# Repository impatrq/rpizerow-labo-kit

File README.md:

# rpizerow-labo-kit

Este repositorio cuenta con los esquematicos y circuitos impresos del kit de desarrollo basado en la Raspberry Pi Zero W.

Dentro se encuentran:

- Esquematico y PCB del kit
- Lista de materiales en .csv
- Archivos .gbr para mandar a produccion el circuito
- Previsualizacion de los Gerber para ver cada capa que se manda a produccion
- Esquematico en .pdf
- Vistas front y bottom con dimensiones y mascara de componentes en .pdf
- Vista de capa bottom copper en .pdf

Trabajo desarrollado por [Agustin Palmieri Hise](https://github.com/agusplay) y [Fabrizio Carlassara](https://github.com/carlassaraf)

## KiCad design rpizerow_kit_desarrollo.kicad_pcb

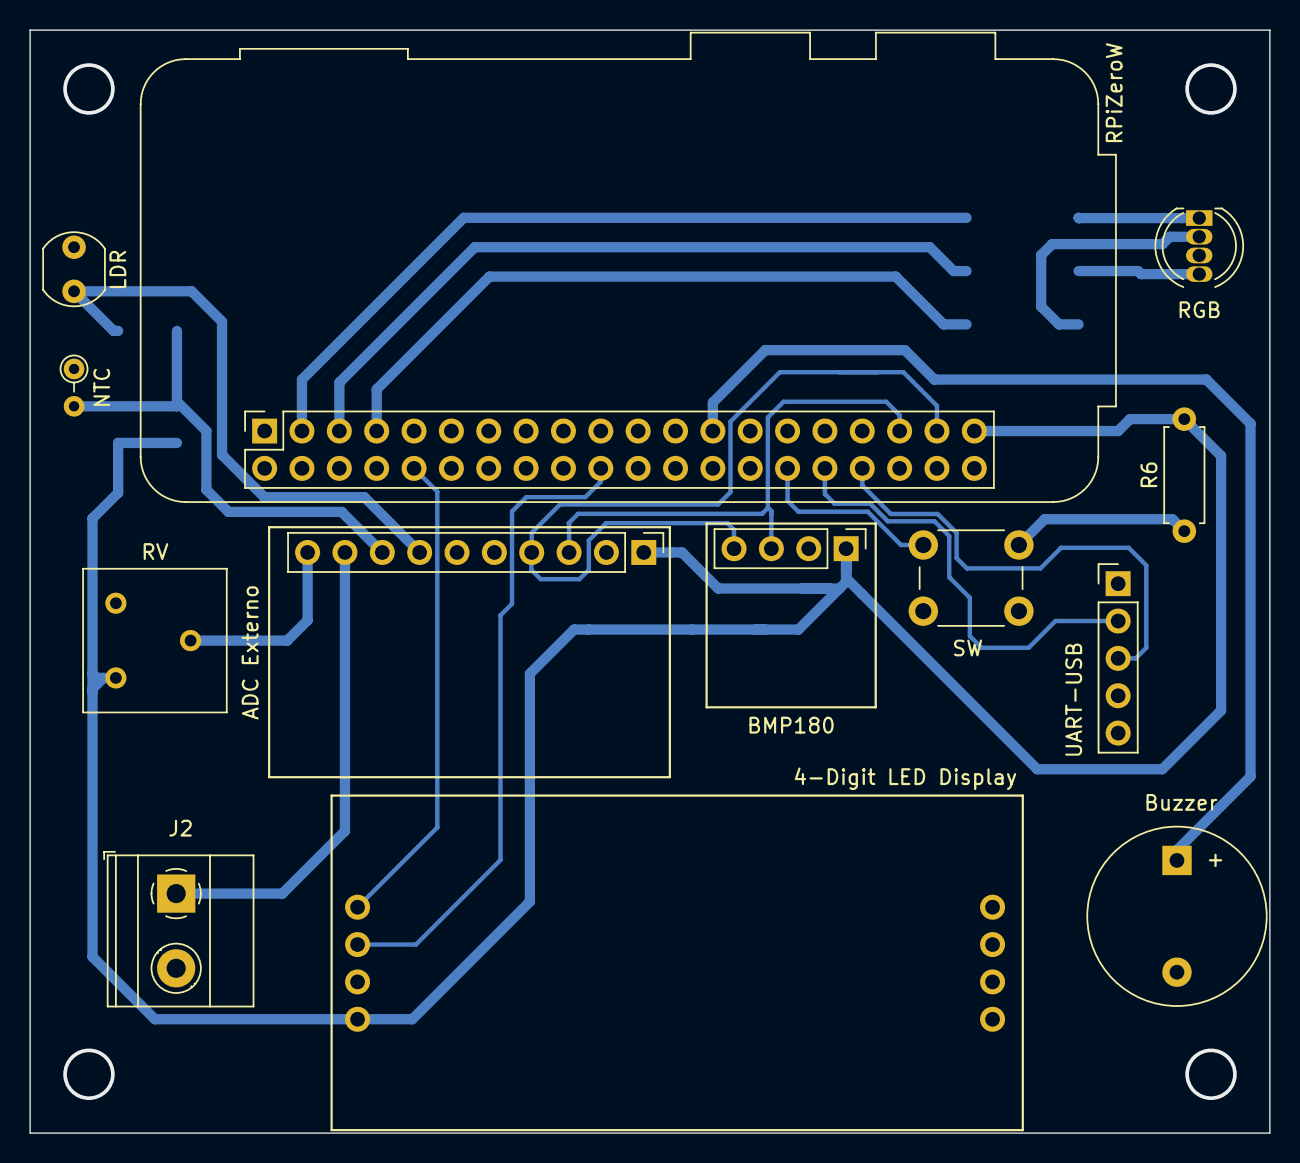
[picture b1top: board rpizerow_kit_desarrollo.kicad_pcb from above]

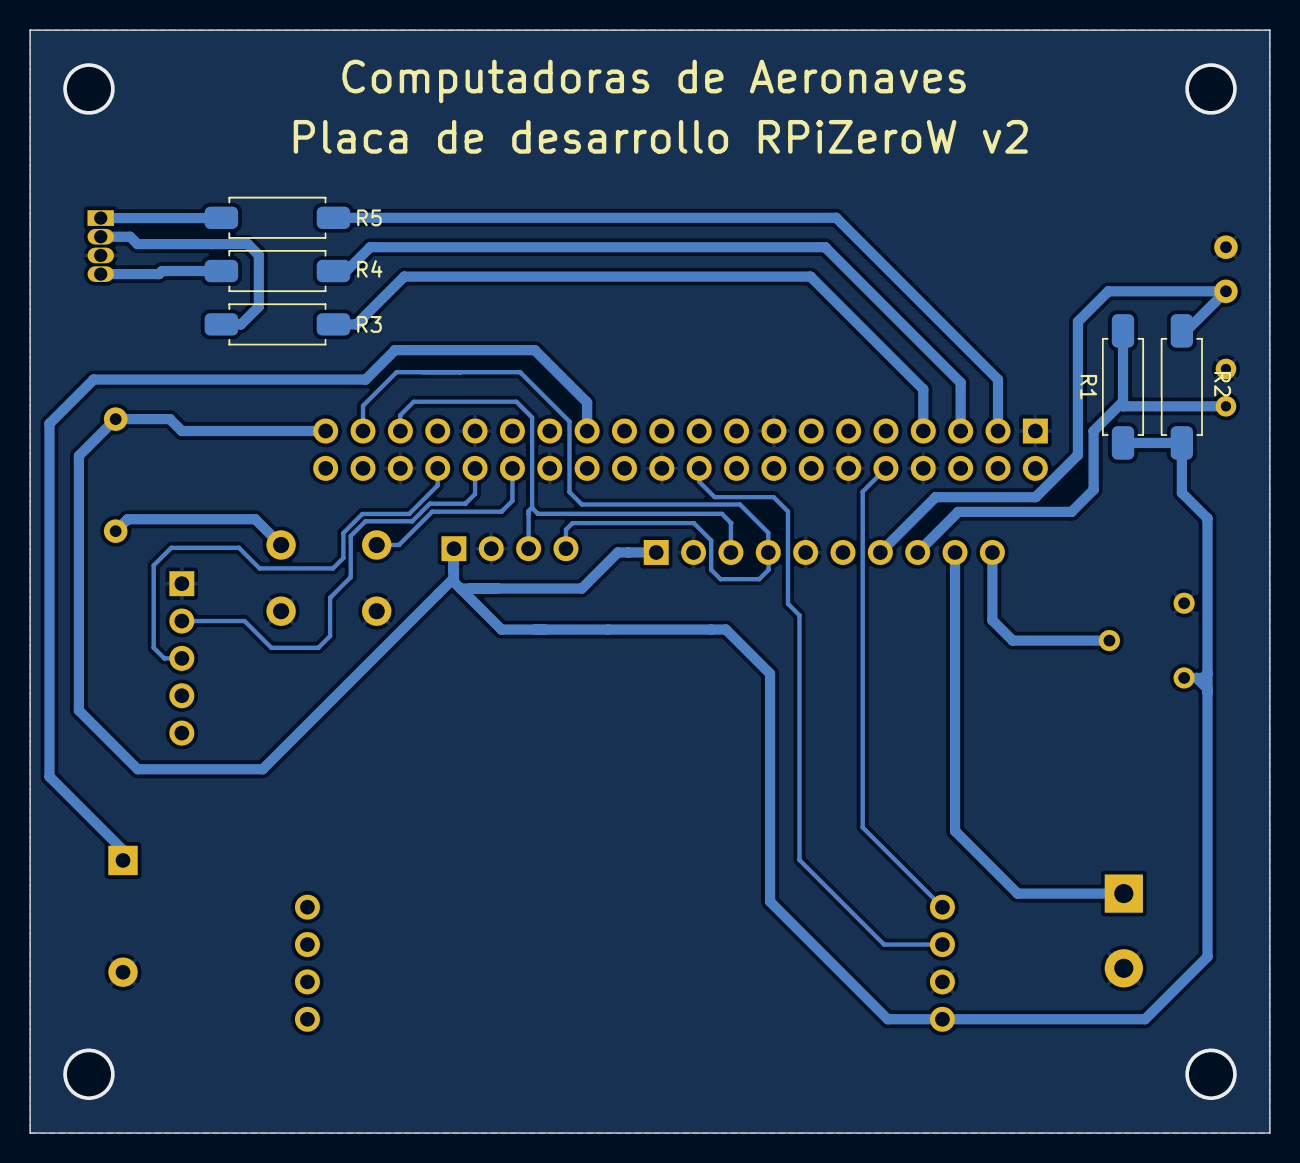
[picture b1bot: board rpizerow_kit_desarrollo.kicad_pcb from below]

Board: 2 copper layers, 84.3 x 75.0 mm, 18 parts (5 on the bottom side), 20 nets.

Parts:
4-Digit LED Display: TM1637
ADC Externo: ADS1115IDGS; PinHeader_1x10_P2.54mm_Vertical
BMP180: BMP 280; PinHeader_1x04_P2.54mm_Vertical
Buzzer: Buzzer; Buzzer_12x9.5RM7.6
J2: Screw_Terminal_01x02; TerminalBlock_Phoenix_MKDS-1,5-2-5.08_1x02_P5.08mm_Horizont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
LDR: A9050; R_LDR_5.0x4.1mm_P3mm_Vertical
NTC: Thermistor; R_Axial_DIN0204_L3.6mm_D1.6mm_P2.54mm_Vertical
R1, R2: 10k; R_Axial_DIN0207_L6.3mm_D2.5mm_P7.62mm_Horizontal
R3, R4, R5: 220; R_Axial_DIN0207_L6.3mm_D2.5mm_P7.62mm_Horizontal
R6: R; R_Axial_DIN0207_L6.3mm_D2.5mm_P7.62mm_Horizontal
RGB: LED_RGB; LED_D5.0mm-4_RGB
RPiZeroW: RPi_GPIO; Raspberry_Pi_Zero_Socketed_THT_FaceDown_MountingHoles
RV: R_Potentiometer; Potentiometer_Bourns_3386F_Vertical
SW: SW_DIP_x01; SW_PUSH_6mm_H13mm
UART-USB: Conector USB; PinHeader_1x05_P2.54mm_Vertical

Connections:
+3.3V: 4-Digit LED Display.1, ADC Externo.8 (VDD), BMP180.1, R1.1, R2.1, R6.2, RPiZeroW.1 (3.3V), RPiZeroW.17 (3.3V), RV.1
CLK: 4-Digit LED Display.4, RPiZeroW.32 (GPIO12)
DIO: 4-Digit LED Display.3, RPiZeroW.22 (GPIO25)
GND: 4-Digit LED Display.2, ADC Externo.1 (ADDR), ADC Externo.3 (GND), BMP180.2, Buzzer.2 (+), J2.1, LDR.2, NTC.1, RGB.2, RPiZeroW.6 (GND), RPiZeroW.9 (GND), RPiZeroW.14 (GND), RPiZeroW.20 (GND), RPiZeroW.25 (GND), RPiZeroW.30 (GND), RPiZeroW.34 (GND), RPiZeroW.39 (GND), RV.3, SW.2, UART-USB.1
I2C SCL: ADC Externo.10 (SCL), BMP180.3, RPiZeroW.5 (GPIO03_SCL1_I2C)
I2C SDA: ADC Externo.9 (SDA), BMP180.4, RPiZeroW.3 (GPIO02_SDA1_I2C)
I/O 12: Buzzer.1 (-), RPiZeroW.15 (GPIO22)
I/O 13: R6.1, RPiZeroW.12 (GPIO18), SW.1
unnamed: R3.2, RGB.3
unnamed: R4.2, RGB.1 (BA)
unnamed: R5.2, RGB.4 (RK)
unnamed: ADC Externo.6 (AIN2), J2.2
unnamed: ADC Externo.4 (AIN0), LDR.1, R2.2
unnamed: ADC Externo.5 (AIN1), NTC.2, R1.2
unnamed: ADC Externo.7 (AIN3), RV.2
PWM 1: R3.1, RPiZeroW.33 (GPIO13)
PWM 2: R4.1, RPiZeroW.35 (GPIO19)
PWM 3: R5.1, RPiZeroW.37 (GPIO26)
UART Rx: RPiZeroW.10 (GPIO15_RXD0), UART-USB.2
UART Tx: RPiZeroW.8 (GPIO14_TXD0), UART-USB.3

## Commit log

2023-12-27 esquematico v2
2023-12-27 pcb version 2
2023-12-27 gerbers para mandar a produccion
2023-12-27 ignoro backups y otros
2023-12-27 inicializacion de proyecto
2023-12-27 ignoro cache
2023-12-27 elimino .xml
2023-12-27 agrego huella a rgb
2023-12-27 actualizo por huella de rgb
2023-12-27 .xml del proyecto
2023-12-27 agrego vistas de los gerbers
2023-12-27 vistas de esquematico y pcb en pdf
2023-12-27 readme file
2024-01-19 corrijo RGB
2024-01-19 corrijo etiquetas
2024-01-19 corrijo valor de resistencias
2024-01-19 corrijo bom
2024-01-19 actualizo esquematico
